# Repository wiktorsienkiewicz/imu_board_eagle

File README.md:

# imu_board_eagle
Eagle project for imu_board

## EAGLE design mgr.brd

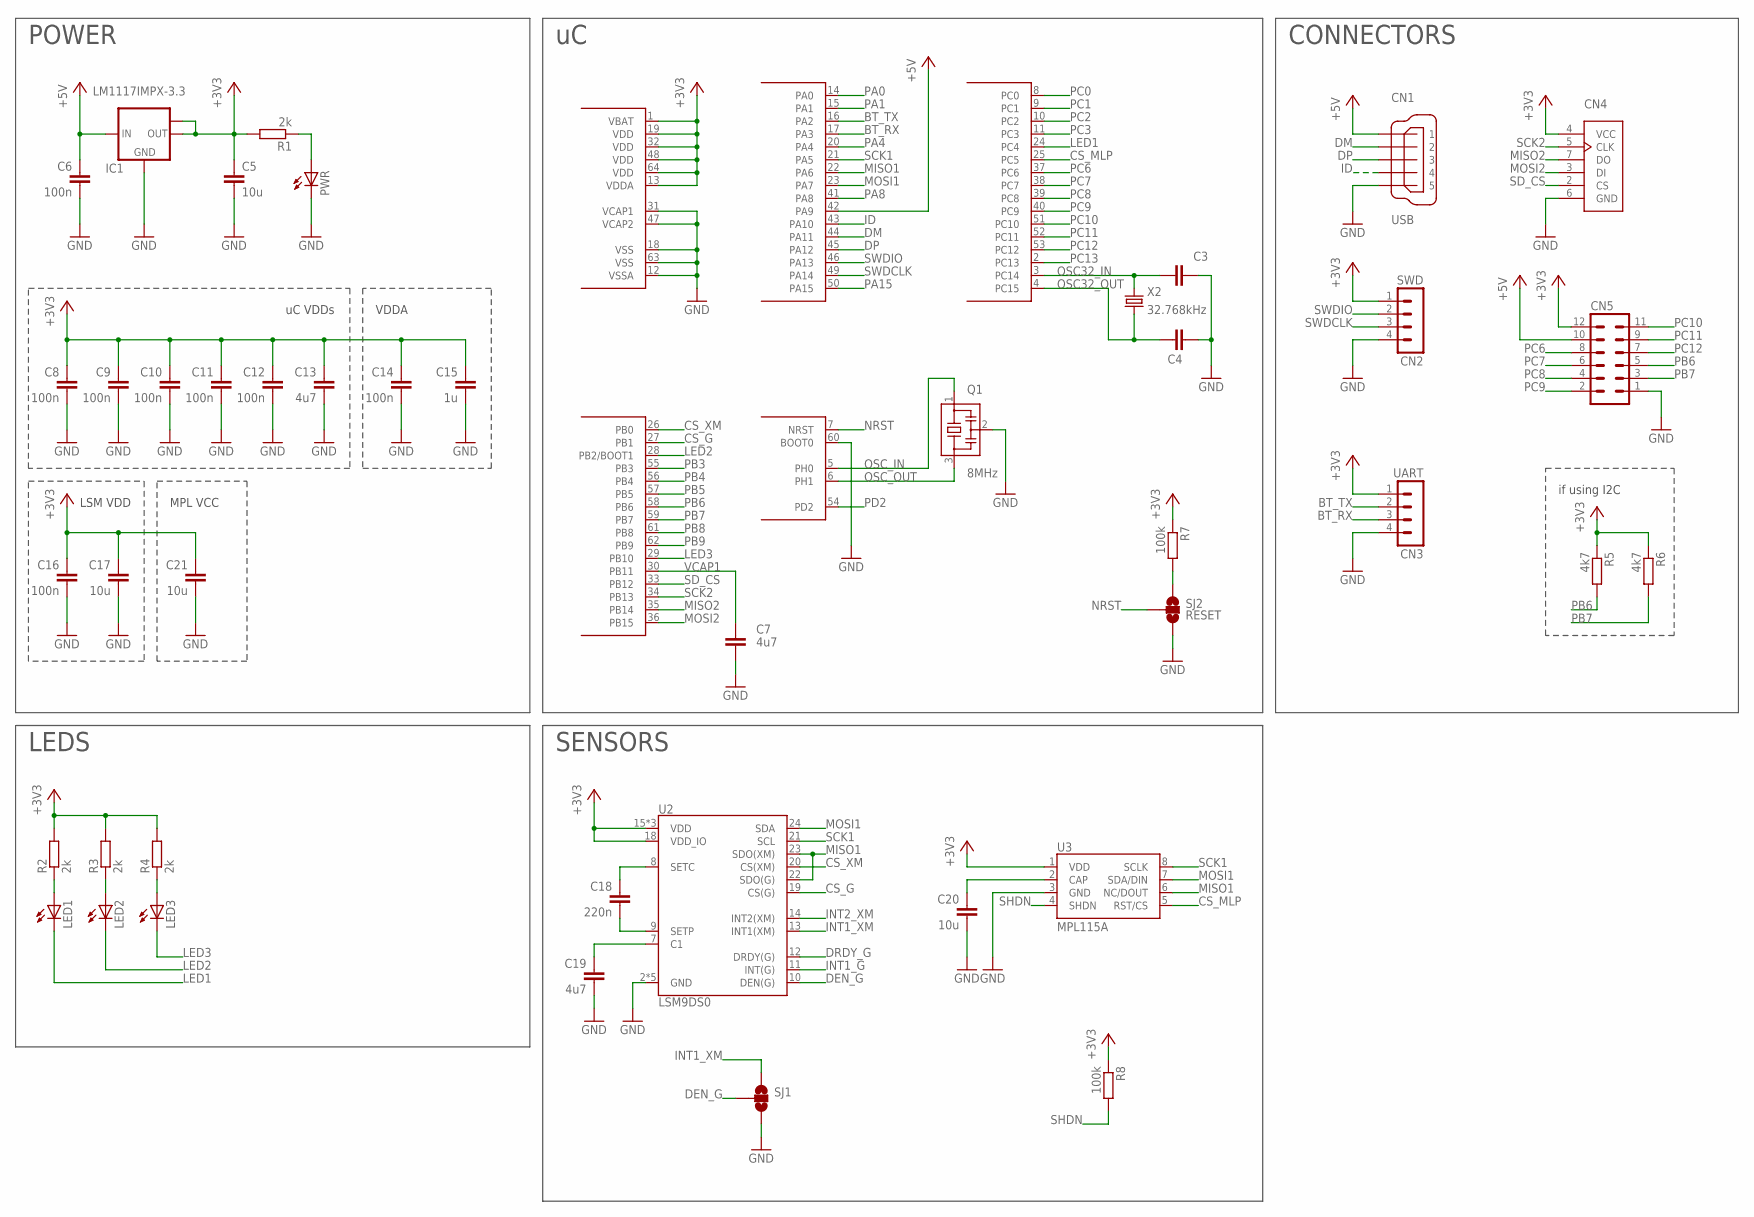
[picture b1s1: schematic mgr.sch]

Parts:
C3, C4: C-EUC0603K; C0603K
C5, C17, C20, C21: 10u; C0603K
C6, C8, C9, C10, C11, C12, C14, C16: 100n; C0603K
C7, C13, C19: 4u7; C0603K
C15: 1u; C0603K
C18: 220n; C0603K
CN1: USB; UX60-MB-5ST
CN2: SWD; MA04-1
CN3: UART; MA04-1
CN4: MICRO_SD_CONNECTOR; MICROSD_CONNECTOR
CN5: MA06-2
IC1: LM1117IMPX-3.3; SOT223
LED1, LED2, LED3: LEDSML0603; SML0603
PWR: LEDSML0603; SML0603
Q1: 8MHz; CSTCR6M
R1, R2, R3, R4: 2k; R0603
R5, R6: 4k7; R0603
R7, R8: 100k; R0603
SJ1: JUMPER-PAD-3-NOYES_SILK; PAD-JUMPER-3-NO_YES_SILK
SJ2: RESET; PAD-JUMPER-3-NO_YES_SILK
U1: STM32F4-64; SQFP-S-10X10-64
U2: LSM9DS0; LGA-24
U3: MPL115A; LGA8
X2: 32.768kHz; 3.2X1.5-2-PAD

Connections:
+3V3: C5.2, C8.2, C9.2, C10.2, C11.2, C12.2, C13.2, C14.2, C15.2, C16.2, C17.2, C21.2, CN2.1, CN3.1, CN4.4 (VCC), CN5.12, IC1.2 (OUT), IC1.TAB (OUT1), R1.2, R2.2, R3.2, R4.2, R5.1, R6.1, R7.1, R8.1, U1.1 (VBAT), U1.13 (VDDA), U1.19 (VDD), U1.32 (VDD), U1.48 (VDD), U1.64 (VDD), U2.15 (VDD), U2.16 (VDD), U2.17 (VDD), U2.18 (VDD_IO), U3.1 (VDD)
+5V: C6.2, CN1.1, CN5.10, IC1.3 (IN), U1.42 (PA9)
BT_RX: CN3.3, U1.17 (PA3)
BT_TX: CN3.2, U1.16 (PA2)
CS_G: U1.27 (PB1), U2.19 (CS(G))
CS_MLP: U1.25 (PC5), U3.5 (RST/CS)
CS_XM: U1.26 (PB0), U2.20 (CS(XM))
DEN_G: SJ1.2, U2.10 (DEN(G))
DM: CN1.2, U1.44 (PA11)
DP: CN1.3, U1.45 (PA12)
DRDY_G: U2.12 (DRDY(G))
GND: C3.2, C4.2, C5.1, C6.1, C7.2, C8.1, C9.1, C10.1, C11.1, C12.1, C13.1, C14.1, C15.1, C16.1, C17.1, C19.1, C20.1, C21.1, CN1.5, CN2.4, CN3.4, CN4.6 (GND), CN5.1, IC1.1 (GND), PWR.C, Q1.2, SJ1.3, SJ2.3, U1.12 (VSSA), U1.18 (VSS), U1.31 (VCAP1), U1.47 (VCAP2), U1.60 (BOOT0), U1.63 (VSS), U2.2 (GND), U2.3 (GND), U2.4 (GND), U2.5 (GND), U2.6 (GND), U3.3 (GND)
ID: CN1.4, U1.43 (PA10)
INT1_G: U2.11 (INT(G))
INT1_XM: SJ1.1, U2.13 (INT1(XM))
INT2_XM: U2.14 (INT2(XM))
LED1: LED1.C, U1.24 (PC4)
LED2: LED2.C, U1.28 (PB2/BOOT1)
LED3: LED3.C, U1.29 (PB10)
MISO1: U1.22 (PA6), U2.22 (SDO(G)), U2.23 (SDO(XM)), U3.6 (NC/DOUT)
MISO2: CN4.7 (DO), U1.35 (PB14)
MOSI1: U1.23 (PA7), U2.24 (SDA), U3.7 (SDA/DIN)
MOSI2: CN4.3 (DI), U1.36 (PB15)
unnamed: PWR.A, R1.1
unnamed: C19.2, U2.7 (C1)
unnamed: C18.1, U2.9 (SETP)
unnamed: C18.2, U2.8 (SETC)
unnamed: LED1.A, R2.1
unnamed: LED2.A, R3.1
unnamed: LED3.A, R4.1
unnamed: C20.2, U3.2 (CAP)
unnamed: R7.2, SJ2.1
NRST: SJ2.2, U1.7 (NRST)
OSC32_IN: C3.1, U1.3 (PC14), X2.1
OSC32_OUT: C4.1, U1.4 (PC15), X2.2
OSC_IN: Q1.1, U1.5 (PH0)
OSC_OUT: Q1.3, U1.6 (PH1)
PA0: U1.14 (PA0)
PA1: U1.15 (PA1)
PA4: U1.20 (PA4)
PA8: U1.41 (PA8)
PA15: U1.50 (PA15)
PB3: U1.55 (PB3)
PB4: U1.56 (PB4)
PB5: U1.57 (PB5)
PB6: CN5.5, R5.2, U1.58 (PB6)
PB7: CN5.3, R6.2, U1.59 (PB7)
PB8: U1.61 (PB8)
PB9: U1.62 (PB9)
PC0: U1.8 (PC0)
PC1: U1.9 (PC1)
PC2: U1.10 (PC2)
PC3: U1.11 (PC3)
PC6: CN5.8, U1.37 (PC6)
PC7: CN5.6, U1.38 (PC7)
PC8: CN5.4, U1.39 (PC8)
PC9: CN5.2, U1.40 (PC9)
PC10: CN5.11, U1.51 (PC10)
PC11: CN5.9, U1.52 (PC11)
PC12: CN5.7, U1.53 (PC12)
PC13: U1.2 (PC13)
PD2: U1.54 (PD2)
SCK1: U1.21 (PA5), U2.21 (SCL), U3.8 (SCLK)
SCK2: CN4.5 (CLK), U1.34 (PB13)
SD_CS: CN4.2 (CS), U1.33 (PB12)
SHDN: R8.2, U3.4 (SHDN)
SWDCLK: CN2.3, U1.49 (PA14)
SWDIO: CN2.2, U1.46 (PA13)
VCAP1: C7.1, U1.30 (PB11)

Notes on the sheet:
POWER
CONNECTORS
uC VDDs
VDDA
LSM VDD
MPL VCC
SENSORS
LEDS
if using I2C

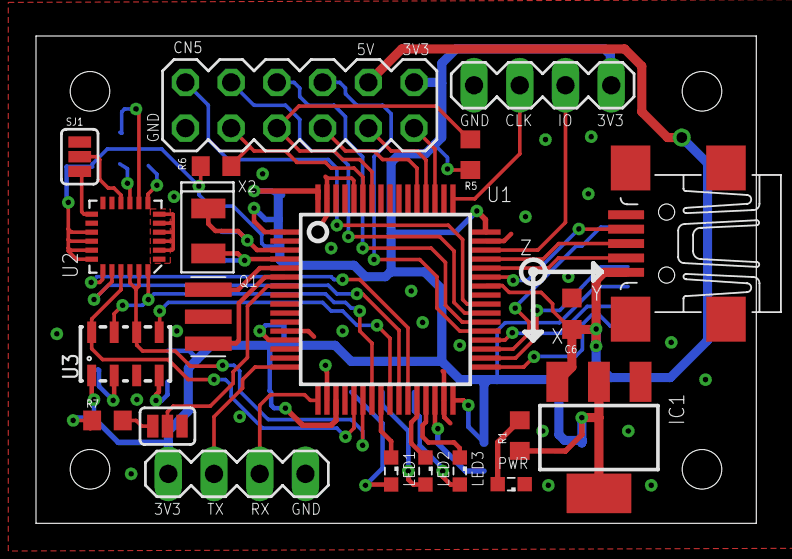
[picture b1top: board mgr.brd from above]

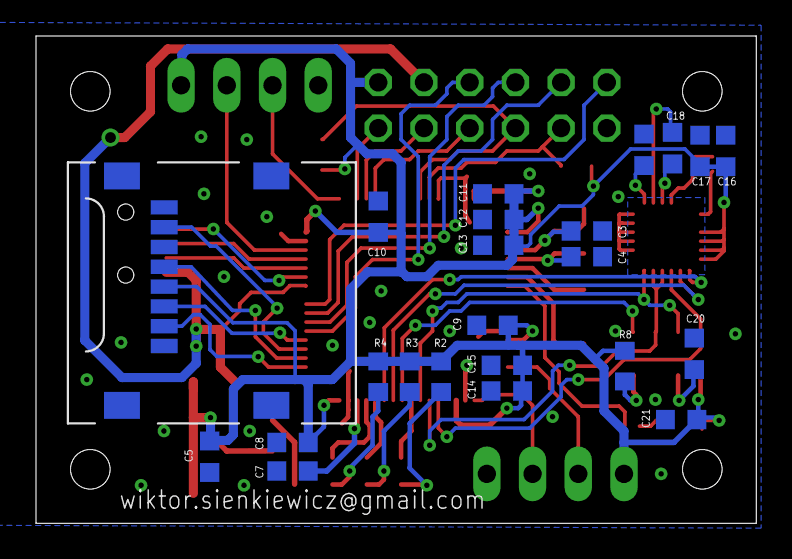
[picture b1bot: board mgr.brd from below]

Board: 2 copper layers, 40.0 x 27.1 mm, 44 parts (23 on the bottom side), 50 nets.

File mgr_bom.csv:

"Qty";"Value";"Device";"Package";"Parts";"Description";"";
"2";"";"C-EUC0603K";"C0603K";"C3, C4";"CAPACITOR, European symbol";"";
"1";"";"JUMPER-PAD-3-NOYES_SILK";"PAD-JUMPER-3-NO_YES_SILK";"SJ1";"";"";
"4";"";"LEDSML0603";"SML0603";"LED1, LED2, LED3, PWR";"LED";"";
"1";"";"MA06-2";"MA06-2";"CN5";"PIN HEADER";"";
"1";"";"STM32F4-64";"SQFP-S-10X10-64";"U1";"STM32F4, 64 pin package";"";
"2";"100k";"R-EU_R0603";"R0603";"R7, R8";"RESISTOR, European symbol";"";
"8";"100n";"C-EUC0603K";"C0603K";"C6, C8, C9, C10, C11, C12, C14, C16";"CAPACITOR, European symbol";"";
"4";"10u";"C-EUC0603K";"C0603K";"C5, C17, C20, C21";"CAPACITOR, European symbol";"";
"1";"1u";"C-EUC0603K";"C0603K";"C15";"CAPACITOR, European symbol";"";
"1";"220n";"C-EUC0603K";"C0603K";"C18";"CAPACITOR, European symbol";"";
"4";"2k";"R-EU_R0603";"R0603";"R1, R2, R3, R4";"RESISTOR, European symbol";"";
"1";"32.768kHz";"CRYSTALS-NOGND-CFPX-217";"3.2X1.5-2-PAD";"X2";"CRYSTALS CAN NOT GROUNDED";"";
"2";"4k7";"R-EU_R0603";"R0603";"R5, R6";"RESISTOR, European symbol";"";
"3";"4u7";"C-EUC0603K";"C0603K";"C7, C13, C19";"CAPACITOR, European symbol";"";
"1";"8MHz";"CSTCR6M00G53Z";"CSTCR6M";"Q1";"Resonator";"";
"1";"LM1117IMPX-3.3";"LM1117IMPX-3.3";"SOT223";"IC1";"";"";
"1";"LSM9DS0";"LSM9DS0";"LGA-24";"U2";"LSM9DS0 3D Accelerometer, 3D Gyroscope, 3D Magnetomter";"";
"1";"MICRO_SD_CONNECTOR";"MICRO_SD_CONNECTOR";"MICROSD_CONNECTOR";"CN4";"MicroSD connector with SPI interface";"";
"1";"MPL115A";"MPL115A";"LGA8";"U3";"MPL115A1 (SPI) and MPL115A2 (I2C) Miniature Digital Barometer";"";
"1";"RESET";"JUMPER-PAD-3-NOYES_SILK";"PAD-JUMPER-3-NO_YES_SILK";"SJ2";"";"";
"1";"SWD";"MA04-1";"MA04-1";"CN2";"PIN HEADER";"";
"1";"UART";"MA04-1";"MA04-1";"CN3";"PIN HEADER";"";
"1";"USB";"MINI-USB-UX60-MB-5ST";"UX60-MB-5ST";"CN1";"MINI USB Connector";"";

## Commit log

2015-04-11 added bom

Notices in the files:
parts and their libraries:
SparkFun-Passives: Licensing: Creative Commons ShareAlike 4.0 International - https://creativecommons.org/licenses/by-sa/4.0
